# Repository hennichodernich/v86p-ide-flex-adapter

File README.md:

# V86P IDE Flex extender

This is a FPC ZIF to pin header adapter to be used in combination with the [V86P IDE controller](https://github.com/hennichodernich/v86p-ide).

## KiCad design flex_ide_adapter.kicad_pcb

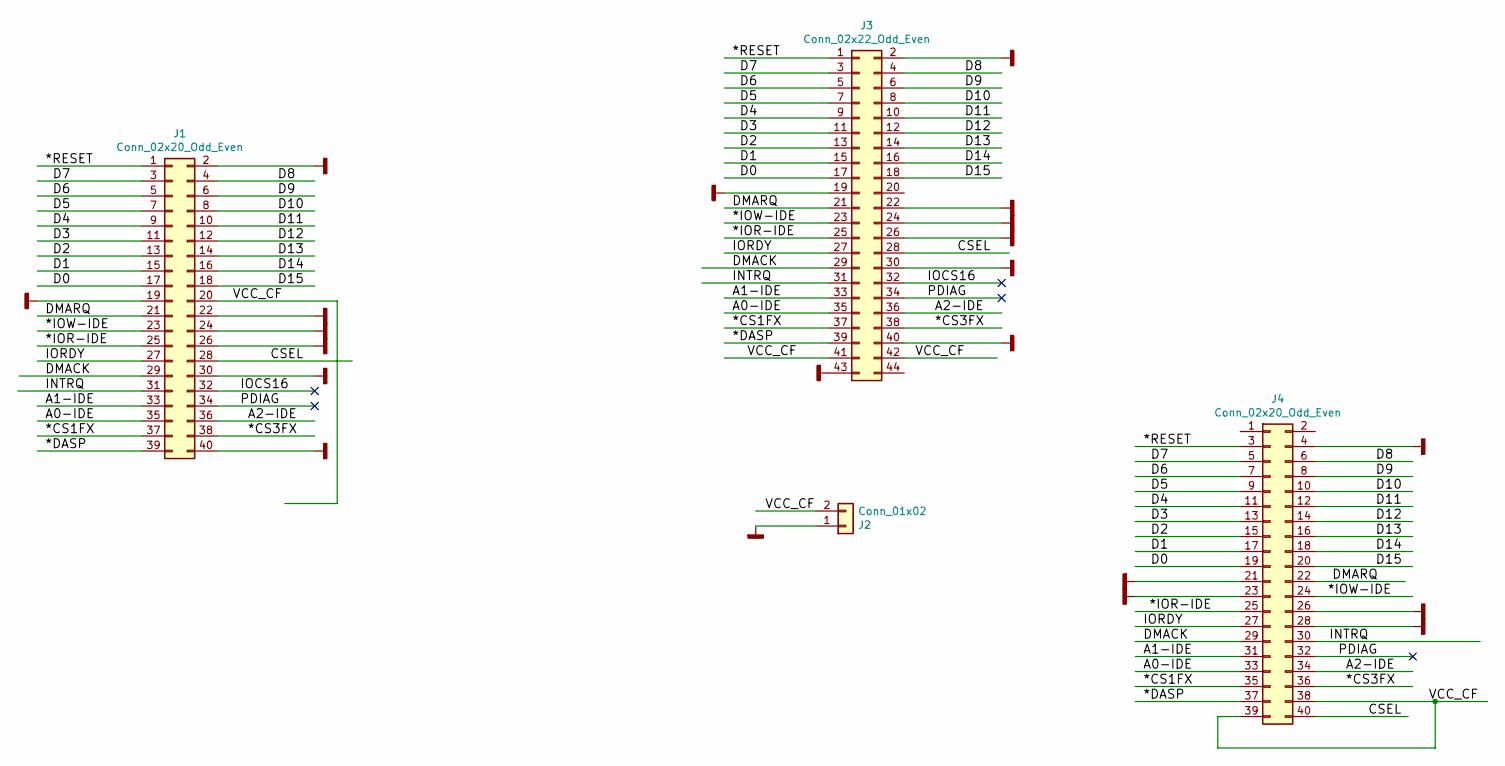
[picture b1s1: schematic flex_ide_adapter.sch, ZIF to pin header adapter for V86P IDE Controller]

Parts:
J1: Conn_02x20_Odd_Even; PinHeader_2x20_P2.54mm_Vertical
J2: Conn_01x02; PinHeader_1x02_P2.54mm_Horizontal
J3: Conn_02x22_Odd_Even; PinSocket_2x22_P2.00mm_Horizontal
J4: Conn_02x20_Odd_Even; TE_4-1734839-0_1x40-1MP_P0.5mm_Horizontal

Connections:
/*CS1FX: J1.37, J3.37, J4.35
/*CS3FX: J1.38, J3.38, J4.36
/*DASP: J1.39, J3.39, J4.37
/*IOR-IDE: J1.25, J3.25, J4.25
/*IOW-IDE: J1.23, J3.23, J4.24
/*RESET: J1.1, J3.1, J4.3
/A0-IDE: J1.35, J3.35, J4.33
/A1-IDE: J1.33, J3.33, J4.31
/A2-IDE: J1.36, J3.36, J4.34
/CSEL: J1.28, J3.28, J4.40
/D0: J1.17, J3.17, J4.19
/D1: J1.15, J3.15, J4.17
/D2: J1.13, J3.13, J4.15
/D3: J1.11, J3.11, J4.13
/D4: J1.9, J3.9, J4.11
/D5: J1.7, J3.7, J4.9
/D6: J1.5, J3.5, J4.7
/D7: J1.3, J3.3, J4.5
/D8: J1.4, J3.4, J4.6
/D9: J1.6, J3.6, J4.8
/D10: J1.8, J3.8, J4.10
/D11: J1.10, J3.10, J4.12
/D12: J1.12, J3.12, J4.14
/D13: J1.14, J3.14, J4.16
/D14: J1.16, J3.16, J4.18
/D15: J1.18, J3.18, J4.20
/DMACK: J1.29, J3.29, J4.29
/DMARQ: J1.21, J3.21, J4.22
/INTRQ: J1.31, J3.31, J4.30
/IOCS16: J1.32, J3.32
/IORDY: J1.27, J3.27, J4.27
/PDIAG: J1.34, J3.34, J4.32
/VCC_CF: J1.20, J2.2, J3.41, J3.42, J4.38, J4.39
GNDD: J1.2, J1.19, J1.22, J1.24, J1.26, J1.30, J1.40, J2.1, J3.2, J3.19, J3.22, J3.24, J3.26, J3.30, J3.40, J3.43, J4.4, J4.21, J4.23, J4.26, J4.28

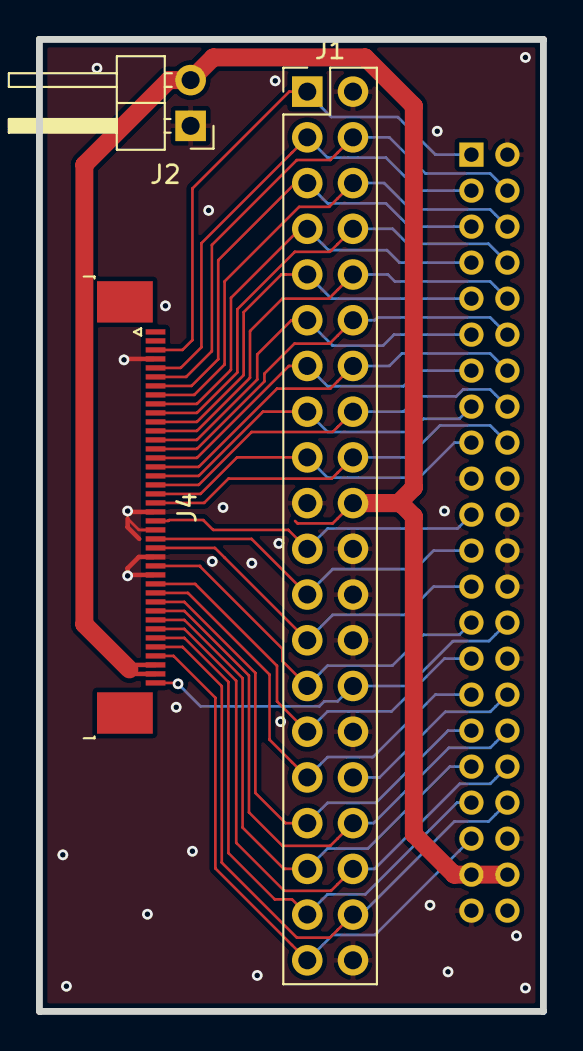
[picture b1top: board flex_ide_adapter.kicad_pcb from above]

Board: 2 copper layers, 28.0 x 54.0 mm, 4 parts (0 on the bottom side), 34 nets.

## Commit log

2020-11-07 First public release.

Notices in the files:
flex_ide_adapter.kicad_pcb:
(c) 2020 hnch@gmx.net
